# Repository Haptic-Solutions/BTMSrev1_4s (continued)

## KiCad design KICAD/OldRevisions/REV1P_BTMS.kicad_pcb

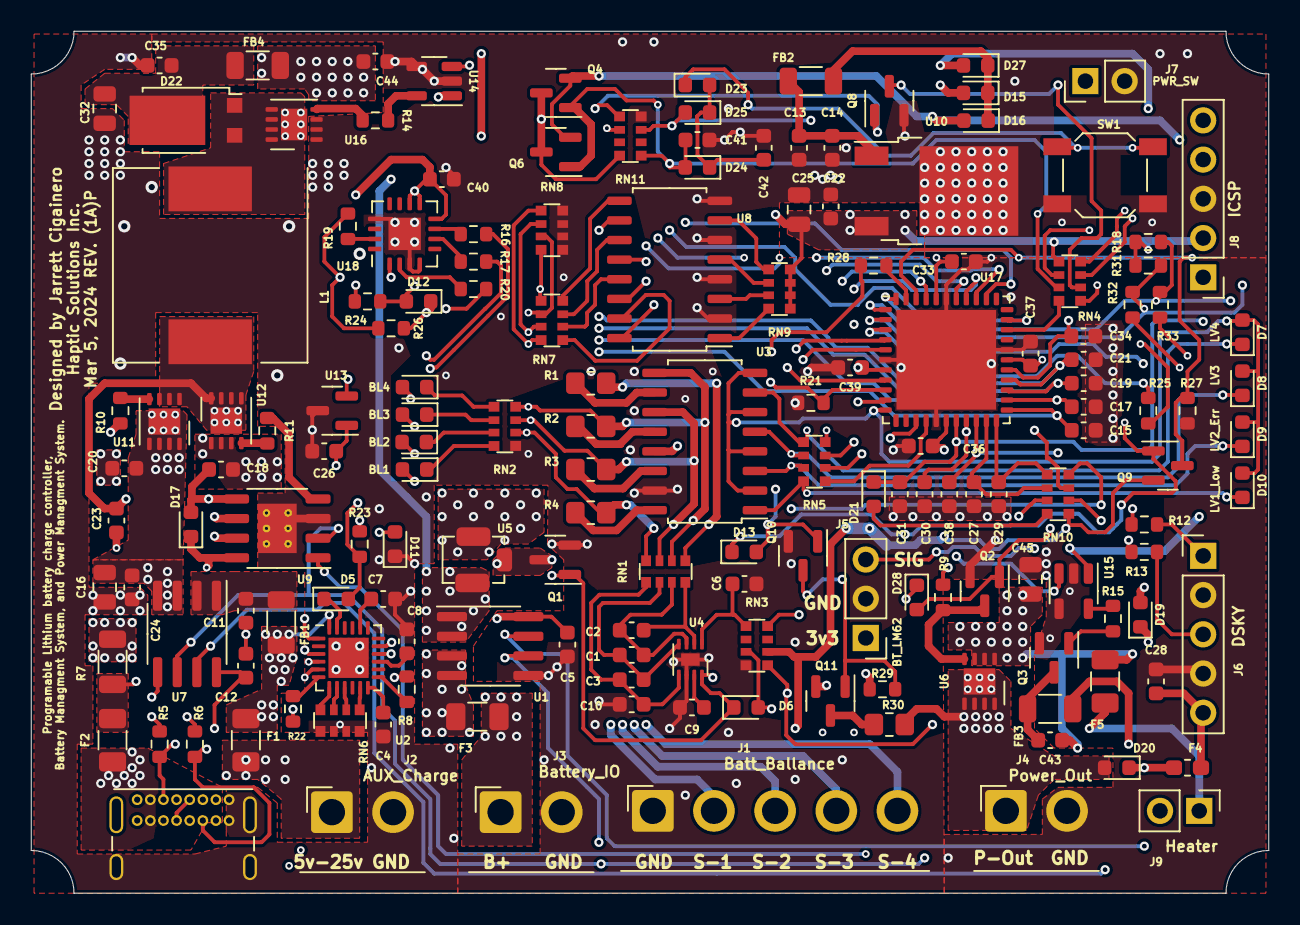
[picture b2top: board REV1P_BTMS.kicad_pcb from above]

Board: 4 copper layers, 80.1 x 55.8 mm, 162 parts (0 on the bottom side), 134 nets.

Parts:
C1, C2, C3, C4, C5, C8, C9, C10, C12, C15, C17, C19, C21, C26, C40, C43: 0.1uf BF; C_0603_1608Metric
C6, C7, C11, C13, C14, C18, C20, C22, C23, C24, C27, C28, C29, C30, C34, C35, C38, C41, C42, C44: 1uf 25v BF; C_0603_1608Metric
C16, C25, C32, C45: 10uf 25v BF; C_0805_2012Metric
C31, C33, C36, C37, C39: 0.1uf film; C_0603_1608Metric
D1: BL4; LED_0603_1608Metric
D2: BL3; LED_0603_1608Metric
D3: BL2; LED_0603_1608Metric
D4: BL1; LED_0603_1608Metric
D5, D6, D13, D15, D16, D17, D19, D20, D21, D23, D24, D25, D27, D28: D_Schottky40V; D_0603_1608Metric
D7: LV4; LED_0603_1608Metric
D8: LV3; LED_0603_1608Metric
D9: LV2_Err; LED_0603_1608Metric
D10: LV1_Low; LED_0603_1608Metric
D11: VB_Stat; LED_0603_1608Metric
D12: Diode40V; D_0603_1608Metric
D22: D_Schottky_AAK; TO-277B
F1, F2, F5: 5A; Fuse_1206_3216Metric
F3: 10A; Fuse_1206_3216Metric
F4: 0A5; Fuse_0603_1608Metric_Pad1.05x0.95mm_HandSolder
FB1, FB2, FB3, FB4: FerriteBead; R_1206_3216Metric
J1: Batt_Ballance; JST_VH_B5PS-VH_1x05_P3.96mm_Horizontal
J2: AUX_Charge; JST_VH_B2PS-VH_1x02_P3.96mm_Horizontal
J3: Battery_IO; JST_VH_B2PS-VH_1x02_P3.96mm_Horizontal
J4: Power_Out; JST_VH_B2PS-VH_1x02_P3.96mm_Horizontal
J5: BT_LM62; PinHeader_1x03_P2.54mm_Vertical
J6: DSKY; PinHeader_1x05_P2.54mm_Vertical
J7: PWR_SW; PinHeader_1x02_P2.54mm_Vertical
J8: ICSP; PinHeader_1x05_P2.54mm_Vertical
J9: Heater; PinHeader_1x02_P2.54mm_Vertical
J10: USB_C_Receptacle_4085; USB_C_Receptacle_GCT_USB4085
L1: 10uH; L_12x12mm_H4.5mm
Q1, Q3: SSM3K341R; SOT-23
Q2, Q8, Q10: DMN65D8L; SOT-23
Q4, Q6, Q9, Q11: FDN340P; SOT-23
R1, R2, R3, R4, R30: 150; R_0805_2012Metric_Pad1.20x1.40mm_HandSolder
R5, R6, R18, R31: 5K1; R_0603_1608Metric
R7: 10mR; R_1206_3216Metric
R8: 10K_NTC; R_0603_1608Metric
R9, R22, R23, R24, R25, R26, R27, R28, R29: 10K; R_0603_1608Metric
R10, R11, R14, R32, R33: 12; R_0603_1608Metric
R12, R13, R15, R16, R17, R19, R20: 27R; R_0603_1608Metric
R21: 91K; R_0603_1608Metric
RN1, RN2, RN3, RN4, RN5, RN6, RN8, RN9, RN10: 1K; R_Array_Convex_4x0612
RN7, RN11: 10K; R_Array_Convex_4x0612
SW1: PTS526; SW_SPST_SKQG_WithStem
U1, U7: ACS711xLCTR-25AB; SOIC-8_3.9x4.9mm_P1.27mm
U2: AP33772; WQFN-24-1EP_4x4mm_P0.5mm_EP2.6x2.6mm
U3, U8: IS281-4; SOIC-16_4.55x10.3mm_P1.27mm
U4: Q294700DSGR; WDFN-8-1EP_2x2mm_P0.5mm_EP0.8x1.2mm
U5: SCF4030-12-0X
U6: AONR21321; DFN-8-1EP_3x3mm_P0.65mm_EP1.7x2.05mm
U9: IRS2184; SOIC-8-1EP_3.9x4.9mm_P1.27mm_EP2.514x3.2mm_ThermalVias
U10: BA033CC0FP-E2; TO-252-2
U11, U12, U16: AON7522E; DFN-8-1EP_3x3mm_P0.65mm_EP1.7x2.05mm
U13: LM62CIM3/NOPB; SOT-23
U14, U15: FAN3100TSX; SOT-23-5
U17: dsPIC30F3011-PT; QFN-44-1EP_8x8mm_P0.65mm_EP6.45x6.45mm
U18: FT230XQ; QFN-16-1EP_4x4mm_P0.65mm_EP2.1x2.1mm

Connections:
+5C: C5.1, C12.1, C22.1, C25.1, C26.1, C33.1, C36.1, C37.1, C39.1, C40.2, D12.1 (K), J5.1, J8.2, Q9.2 (S), R18.1, R23.1, R25.2, R26.2, R31.1, RN3.6 (R3.2), RN4.5 (R4.2), RN9.1 (R1.1), RN9.2 (R2.1), RN9.3 (R3.1), RN9.4 (R4.1), RN10.1 (R1.1), RN11.6 (R3.2), U1.8 (VCC), U7.8 (VCC), U10.3 (VO), U13.1 (G), U17.7 (VDD0), U17.17 (AVDD), U17.28 (VDD1), U17.40 (VDD2), U18.1 (VCCIO), U18.8 (3V3OUT), U18.9 (~RESET), U18.10 (VCC)
/BCsense: C38.1, RN4.6 (R3.2), U17.20 (EMUC3/AN1/VREF-/CN3/RB1)
/BTStrapSig: C23.2, L1.1, U9.6 (VS), U11.1 (S), U11.2 (S), U11.3 (S), U12.5 (D), U12.6 (D), U12.7 (D), U12.8 (D), U12.9 (D)
/BV_Fault: D6.2 (A), RN3.3 (R3.1), U17.36 (~FLTA/INT0/RE8)
/BattIn: F3.2, RN3.8 (R1.2), U1.3 (IP-), U1.4 (IP-)
/Btemp: C27.1, RN10.6 (R3.2), U17.21 (AN2/~SS1/CN4/RB2)
/Btemp_in: J5.3, RN10.3 (R3.1)
/CC1: J10.A5 (CC1), R5.2, U2.17 (CC1)
/CC2: J10.B5 (CC2), R6.2, U2.16 (CC2)
/CCsense: C34.1, RN10.7 (R2.2), U17.27 (AN8/RB8)
/CCsense_in: RN10.2 (R2.1), U7.7 (VIOUT)
/CH_Boost+: U14.3 (IN+), U17.8 (PWM3H/RE5)
/CHctrl+: U9.1 (IN), U17.10 (PWM2H/RE3)
/C_Fault: D13.1 (K), D28.1 (K), Q9.1 (G), RN4.4 (R4.1), U1.6 (~FAULT), U7.6 (~FAULT), U9.2 (~SD)
/C_Fault_In: Q9.3 (D), R27.2, U17.42 (EMUC2/OC1/IC1/INT1/RD0)
/ChargeVoltage: C30.1, D12.2 (A), R24.1, RN3.5 (R4.2), U17.19 (EMUD3/AN0/VREF+/CN2/RB0)
/ExtBus: C43.1, C44.1, C45.1, F5.1, FB4.2, Q11.2 (S), R9.1, R29.1, U5.3 (T2), U6.1 (S), U6.2 (S), U6.3 (S)
/Heat_CTRL: U15.3 (IN+), U17.14 (PWM1H/RE1)
/HighCHfet: R10.2, U11.4 (G)
/IntBus: Q4.3 (D), Q6.3 (D), RN11.8 (R1.2), U1.1 (IP+), U1.2 (IP+), U5.1 (T1)
/IntSwitched: C18.1, D16.2 (A), D17.2 (A), Q4.2 (S), Q6.2 (S), U9.5 (VCC), U14.1 (VDD), U15.1 (VDD)
/KeepAlive: Q8.1 (G), RN11.5 (R4.2), U17.5 (RF0)
/LBatt_Cell_1: D4.2 (A), J1.2, R4.1, RN1.8 (R1.2), RN2.2 (R2.1), U3.13 (out2_E), U8.16 (out1_C)
/LBatt_Cell_2: D3.2 (A), J1.3, R3.1, RN1.7 (R2.2), RN2.3 (R3.1), U3.11 (out3_E), U8.14 (out2_C)
/LBatt_Cell_3: D2.2 (A), J1.4, R2.1, RN1.6 (R3.2), RN2.4 (R4.1), U3.9 (out4_E), U8.12 (out3_C)
/LBatt_Cell_4: D1.2 (A), J1.5, R1.1, RN1.5 (R4.2), U8.10 (out4_C)
/LithCell_V1: C15.1, RN7.8 (R1.2), RN8.1 (R1.1), U17.23 (AN4/QEA/IC7/CN6/RB4)
/LithCell_V2: C17.1, RN7.7 (R2.2), RN8.2 (R2.1), U17.24 (AN5/QEB/IC8/CN7/RB5)
/LithCell_V3: C19.1, RN7.6 (R3.2), RN8.3 (R3.1), U17.25 (AN6/OCFA/RB6)
/LithCell_V4: C21.1, RN7.5 (R4.2), RN8.4 (R4.1), U17.26 (AN7/RB7)
/LowCHfet: R11.2, U12.4 (G)
/MCLR: C31.1, D21.1 (K), J8.1, U17.18 (~MCLR)
/Mult_B1: RN5.1 (R1.1), U17.15 (PWM1L/RE0)
/Mult_B2: RN5.2 (R2.1), U17.37 (EMUD2/OC2/IC2/INT2/RD1)
/Mult_B3: RN5.3 (R3.1), U17.41 (OC3/RD2)
/Mult_B4: RN5.4 (R4.1), U17.38 (OC4/RD3)
/Mult_SEL: D7.2 (A), D8.2 (A), D9.2 (A), D10.2 (A), U3.2 (in1_C), U3.4 (in2_C), U3.6 (in3_C), U3.8 (in4_C), U17.11 (PWM2L/RE2)
/PGMC: J8.5, R31.2, R32.1, U17.1 (PGC/EMUC/U1RX/SDI1/SDA/RF2)
/PGMD: J8.4, R18.2, R33.1, U17.44 (PGD/EMUD/U1TX/SDO1/SCL/RF3)
/PO_EN: D28.2 (A), Q2.1 (G), RN4.1 (R1.1)
/Pctrl_IN: Q8.3 (D), RN4.2 (R2.1)
/Pctrl_OUT: C41.1, D24.2 (A), Q4.1 (G), Q6.1 (G), RN4.7 (R2.2), RN11.1 (R1.1)
/PowerOutEnable: RN4.8 (R1.2), U17.31 (OSC2/CLKO/RC15)
/PowerOutput: D20.2 (A), D27.2 (A), J4.1, R30.2, U6.5 (D), U6.6 (D), U6.7 (D), U6.8 (D), U6.9 (D)
/Pre_Charge: R28.1, U17.43 (SCK1/RF6)
/U1RX: R19.2, R26.1, U17.35 (EMUC1/SOSCO/T1CK/U1ARX/CN0/RC14)
/U1TX: R20.2, U17.32 (EMUD1/SOSCI/T2CK/U1ATX/CN1/RC13)
/U2RX: R12.2, R25.1, U17.3 (U2RX/CN17/RF4)
/U2TX: R13.2, U17.2 (U2TX/CN18/RF5)
/USB_D+: J10.A6 (D+), J10.B6 (D+), R17.1
/USB_D-: J10.A7 (D-), J10.B7 (D-), R16.1
/V_Bus_Stat: D5.2 (A), R21.2, R23.2, U17.9 (PWM3L/RE4)
/__PwrKey: D25.2 (A), RN11.3 (R3.1), U17.4 (RF1)
GND: C4.2, C5.2, C6.2, C7.2, C8.2, C9.2, C10.2, C11.2, C12.2, C13.2, C14.2, C15.2, C16.2, C17.2, C18.2, C19.2, C20.2, C21.2, C22.2, C24.2, C25.2, C26.2, C27.2, C28.2, C29.2, C30.2, C31.2, C32.2, C33.2, C34.2, C35.2, C36.2, C37.2, C38.2, C39.2, C40.1, C41.2, C42.2, C44.2, C45.2, D11.1 (K), J1.1, J2.2, J3.2, J4.2, J5.2, J6.2, J6.4, J7.2, J8.3, J10.A1 (GND), J10.A12 (GND), J10.B1 (GND), J10.B12 (GND), J10.S1 (SHIELD), Q1.2 (S), Q2.2 (S), Q3.2 (S), Q8.2 (S), Q10.2 (S), R5.1, R6.1, R8.1, R21.1, R27.1, RN2.1 (R1.1), RN3.4 (R4.1), RN6.5 (R4.2), RN6.6 (R3.2), RN6.7 (R2.2), RN6.8 (R1.2), RN8.5 (R4.2), RN8.6 (R3.2), RN8.7 (R2.2), RN8.8 (R1.2), RN11.4 (R4.1), SW1.1 (A), U1.5 (GND), U2.3 (GND), U2.25 (PAD), U3.15 (out1_E), U4.6 (VSS), U4.9 (PAD), U7.5 (GND), U8.2 (in1_C), U8.4 (in2_C), U8.6 (in3_C), U8.8 (in4_C), U9.3 (COM), U9.9 (PAD), U10.2 (GND), U12.1 (S), U12.2 (S), U12.3 (S), U13.3 (S), U14.2 (GND), U14.4 (XREF), U15.2 (GND), U15.4 (XREF), U16.1 (S), U16.2 (S), U16.3 (S), U17.6 (VSS0), U17.16 (AVSS), U17.29 (VSS1), U17.39 (VSS2), U17.45 (PAD), U18.3 (GND), U18.4 (~CTS), U18.13 (GND), U18.17 (GND)
unnamed: C1.1, C3.2, RN1.2 (R2.1), U4.4 (V2)
unnamed: C1.2, C2.1, RN1.3 (R3.1), U4.3 (V3)
unnamed: C2.2, RN1.4 (R4.1), U4.2 (V4)
unnamed: C6.1, RN3.1 (R1.1), U4.1 (VDD)
unnamed: C7.1, U2.20 (V5V)
unnamed: C8.1, U2.15 (IFB)
unnamed: C9.1, U4.7 (CD)
unnamed: C3.1, C10.1, RN1.1 (R1.1), U4.5 (V1)
unnamed: C11.1, FB1.2, U7.1 (IP+), U7.2 (IP+)
unnamed: C13.1, C14.1, FB2.2, U10.1 (VI)
unnamed: C16.1, C20.1, C24.1, U7.3 (IP-), U7.4 (IP-), U11.5 (D), U11.6 (D), U11.7 (D), U11.8 (D), U11.9 (D)
unnamed: C23.1, D17.1 (K), U9.8 (VB)
unnamed: C28.1, F4.2, J6.5
unnamed: C29.1, RN10.5 (R4.2), U17.22 (AN3/INDX/CN5/RB3)
unnamed: C32.1, C35.1, D22.3 (K), FB4.1
unnamed: C42.1, D23.2 (A), D24.1 (K), D25.1 (K)
unnamed: C43.2, FB3.1, Q3.3 (D)
unnamed: D1.1 (K), RN2.5 (R4.2)
unnamed: D2.1 (K), RN2.6 (R3.2)
unnamed: D3.1 (K), RN2.7 (R2.2)
unnamed: D4.1 (K), RN2.8 (R1.2)
unnamed: D5.1 (K), U2.23 (PWR_EN)
unnamed: D6.1 (K), Q1.1 (G), U4.8 (OUT)
unnamed: D7.1 (K), RN5.5 (R4.2), U3.7 (in4_A)
unnamed: D8.1 (K), RN5.6 (R3.2), U3.5 (in3_A)
unnamed: D9.1 (K), RN5.7 (R2.2), U3.3 (in2_A)
unnamed: D10.1 (K), RN5.8 (R1.2), U3.1 (in1_A)
unnamed: D11.2 (A), R22.1
unnamed: D13.2 (A), Q10.1 (G), R28.2
unnamed: D15.1 (K), D16.1 (K), D27.1 (K), FB2.1
unnamed: D19.1 (K), D20.1 (K), F4.1
unnamed: D21.2 (A), RN10.8 (R1.2)
unnamed: D22.1 (A), D22.2 (A), L1.2, U16.5 (D), U16.6 (D), U16.7 (D), U16.8 (D), U16.9 (D)
unnamed: D23.1 (K), J7.1, SW1.2 (B)
unnamed: F1.1, J2.1
unnamed: F2.1, J10.A4 (VBUS), J10.A9 (VBUS), J10.B4 (VBUS), J10.B9 (VBUS)
unnamed: F2.2, R7.2, U2.1 (ISENP)
unnamed: F3.1, J3.1
unnamed: F5.2, J9.1
unnamed: FB3.2, J9.2
unnamed: J6.1, R12.1
unnamed: J6.3, R13.1
unnamed: Q1.3 (D), U5.2 (Trig)
unnamed: Q2.3 (D), R9.2, U6.4 (G)
unnamed: Q3.1 (G), R15.2
unnamed: Q10.3 (D), Q11.1 (G), R29.2
unnamed: Q11.3 (D), R30.1
unnamed: R1.2, U3.10 (out4_C)
unnamed: R2.2, U3.12 (out3_C)
unnamed: R3.2, U3.14 (out2_C)
unnamed: R4.2, U3.16 (out1_C)
unnamed: R8.2, U2.13 (OTP)
unnamed: R10.1, U9.7 (HO)
unnamed: R11.1, U9.4 (LO)
unnamed: R14.1, U16.4 (G)
unnamed: R14.2, U14.5 (OUT)
unnamed: R15.1, U15.5 (OUT)
unnamed: R16.2, U18.7 (USBDM)
unnamed: R17.2, U18.6 (USBDP)
unnamed: R19.1, U18.15 (TXD)
unnamed: R20.1, U18.2 (RXD)
unnamed: R22.2, U2.6 (GPIO4)
unnamed: RN4.3 (R3.1), U1.7 (VIOUT)
unnamed: RN7.1 (R1.1), U8.15 (out1_E)
unnamed: RN7.2 (R2.1), U8.13 (out2_E)
unnamed: RN7.3 (R3.1), U8.11 (out3_E)
unnamed: RN7.4 (R4.1), U8.9 (out4_E)
unnamed: RN9.5 (R4.2), U8.7 (in4_A)
unnamed: RN9.6 (R3.2), U8.5 (in3_A)
unnamed: RN9.7 (R2.2), U8.3 (in2_A)
unnamed: RN9.8 (R1.2), U8.1 (in1_A)
unnamed: RN10.4 (R4.1), U13.2 (D)
unnamed: R32.2, U2.4 (SDA)
unnamed: R33.2, U2.5 (SCL)
unnamed: RN6.4 (R4.1), U2.7 (GPIO2)
unnamed: RN6.3 (R3.1), U2.8 (GPIO1)
unnamed: RN6.2 (R2.1), U2.9 (GPIO3)
unnamed: RN6.1 (R1.1), U2.11 (GPIO5)
unnamed: C4.1, U2.12 (V3VD)
VBUS: D15.2 (A), D19.2 (A), F1.2, FB1.1, R7.1, R24.2, U2.24 (VCC)

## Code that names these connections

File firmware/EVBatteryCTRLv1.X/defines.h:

/*Copyright (c) <2024> <Jarrett Cigainero>

Permission is hereby granted, free of charge, to any person obtaining a copy
of this software and associated documentation files (the "Software"), to deal
in the Software without restriction, including without limitation the rights
to use, copy, modify, merge, publish, distribute, sublicense, and/or sell
copies of the Software, and to permit persons to whom the Software is
furnished to do so, subject to the following conditions:

The above copyright notice and this permission notice shall be included in all
copies or substantial portions of the Software.

THE SOFTWARE IS PROVIDED "AS IS", WITHO70054eUT WARRANTY OF ANY KIND, EXPRESS OR
IMPLIED, INCLUDING BUT NOT LIMITED TO THE WARRANTIES OF MERCHANTABILITY,
FITNESS FOR A PARTICULAR PURPOSE AND NONINFRINGEMENT. IN NO EVENT SHALL THE
AUTHORS OR COPYRIGHT HOLDERS BE LIABLE FOR ANY CLAIM, DAMAGES OR OTHER
LIABILITY, WHETHER IN AN ACTION OF CONTRACT, TORT OR OTHERWISE, ARISING FROM,
OUT OF OR IN CONNECTION WITH THE SOFTWARE OR THE USE OR OTHER DEALINGS IN THE
SOFTWARE. */

#ifndef DEFINES_H
#define	DEFINES_H
//##############################################################################
// Tm = 32767 * (1 / (((clkSpeedmhz * PLL) / 4) / tiksPerIRQ))
//#define IPS 29.48;   //million instructions per second.
#define IPS 14.74   //million instructions per second.
//Analog
#define sample_Average 2
//PWM period
#define PWM_Period 100
#define PWM_MaxHeat (PWM_Period*2)*0.9
#define PWM_MaxChrg (PWM_Period*2)*0.98
#define PWM_MaxBoost_LO 0.52
#define PWM_MaxBoost_HI 0.72
#define PWM_MaxBoost_LN (PWM_Period*2)*PWM_MaxBoost_LO
#define PWM_MaxBoost_HN (PWM_Period*2)*PWM_MaxBoost_HI
//Charger
#define charge_Max_Level 0.65
#define C_Min_Voltage 3.0
//#define IPS 7.37   //million instructions per second.
#define BAUD1 9600  //Default BAUD rate for PORT 1
#define BAUD2 9600  //Default BAUD rate for PORT 2
#define calc_125 0.00003472 //Value for calculating the total current in and out of battery every second.
//Firmware Version String
#define version "\n\rFirmware: V0.1-Dev\n\r2S-4S Compatible Cell Configs.\n\r(C) Haptic Solutions Inc. (2024)\n\r"
//IO inputs
#define PWR_SW !PORTFbits.RF1 //Power on/off switch, button, or key. Active low input.
#define BV_Fault PORTEbits.RE8  //Battery Voltage Fault.
#define C_Fault PORTDbits.RD0 //Battery or charge input/output current fault.
//Analog inputs
#define ChargeVoltage ADCBUF0 //Voltage
#define BCsense ADCBUF1 //Current
#define Btemp ADCBUF2 //Batt Temp
#define Mtemp ADCBUF3 //My Temp
#define LithCell_V1 ADCBUF4 //Cell 1 Volts
#define LithCell_V2 ADCBUF5 //Cell 2 Volts
#define LithCell_V3 ADCBUF6 //Cell 3 Volts
#define LithCell_V4 ADCBUF7 //Cell 4 Volts
#define CCsense ADCBUF8 //CCsense
//IO outputs
#define KeepAlive LATFbits.LATF0 //Enables power to self and system.
#define Cell_Volt LATEbits.LATE4 //Cell voltage sense enable.
#define PowerOutPreCharge LATFbits.LATF6 //Power output pre-charge control
#define PowerOutEnable LATCbits.LATC15 //Power output enable.
//LED outputs
#define Mult_SEL LATEbits.LATE2 //LED and Cell ballance multiplexed select.
#define Mult_B1 LATEbits.LATE0
#define Mult_B3 LATDbits.LATD2
#define Mult_B2 LATDbits.LATD1
#define Mult_B4 LATDbits.LATD3
#define LED_dir_1 TRISE
#define LED_dir_2 TRISD
#define LED_HiZ_1 PWM_TRIS_DIR | 0x0001
#define LED_HiZ_2 GENERAL3_DIR | 0x000E
#define DFLT_1 PWM_TRIS_DIR
#define DFLT_2 GENERAL3_DIR

#define Heat_CTRL PDC1  //Heater PWM.
#define CHctrl PDC2     //Charge buck PWM.
#define CH_Boost PDC3   //Charge boost PWM.

//IO
#define ANALOG_DIR 0x01FF
#define ANALOG_TRIS TRISB
#define ANALOG_LAT LATB
#define ANALOG_PORT PORTB

#define GENERAL1_DIR 0x1FFF
#define GENERAL1_TRIS TRISC
#define GENERAL1_LAT LATC
#define GENERAL1_PORT PORTC

#define GENERAL2_DIR 0xFFBE
#define GENERAL2_TRIS TRISF
#define GENERAL2_LAT LATF
#define GENERAL2_PORT PORTF

#define GENERAL3_DIR 0xFFF1
#define GENERAL3_TRIS TRISD
#define GENERAL3_LAT LATD
#define GENERAL3_PORT PORTD

#define PWM_TRIS_DIR 0xFFEA
#define PWM_TRIS TRISE
#define PWM_LAT LATE
#define PWM_PORT PORTE

//Memory Defines
/* This assumes the compiler puts the stack at the end of memory space just after
 * the user variables and the stack pointer counts up */
#define ramSize 0x07F0 //Size of memory.
#define ramAddressStart 0x0800  //Where the dsPIC30F4011's ram address starts.
#define stackFaultMax ramSize + ramAddressStart - 1
#define ramFree (ramSize + ramAddressStart) - 2 //Minus 15 bytes of ram. If the stack intrudes on this then it should throw an error code before a complete system crash and undefined behavior.

//General
#define yes 1
#define no 0
#define none 0
#define Ltest 4
#define Debug 3
#define Ballance 2
#define on 1
#define off 0
#define set 1
#define clear 0
#define NULL 0
#define input 1
#define output 0
#define maxFCodes 20
#define I_Auto -1

//Constants
#define Max_Cell_Count 4
#define SOC_Cycles 8
#define AuxFuse 5       //Aux charge port fuse rating placeholder.
#define PreChargeTime 2 //Output pre-charge timer placeholder.
#define LED_Brightness 10
#define V_REF 3.35      //Measured reference voltage placeholder

//Run Levels
#define Shutdown 0
#define Crit_Err 1
#define Heartbeat 2
#define Cal_Mode 3
#define On_W_Err 4
#define All_Sys_Go 5

//Charge Session Levels
#define UnknownStart 0
#define EmptyStart 1
#define FullStart 2

//Heater calibration states.
#define notrun 0
#define initialize 1
#define calibrating 2
#define ready 3
#define error 4
#define disabled 5

//Charger modes.
#define CHError 0
#define Stop 1
#define Wait 2
#define Assignment_Ready 3
#define USB2 4
#define USB3_Wimp 5
#define USB3 6
#define USB3_Fast 7
#define Solar 8
//Charger limits
#define cycleLimit 4

//OSC modes
#define slow 0
#define fast 1

//Power switch modes
#define push_and_hold 0         //Push button switch
#define toggle_switch 1         //Toggle switch
#define on_with_charger 2       //??? what would you use this for?
#define off_with_charger 3      //Solar light, or Emergency light mode.

#define gauge_timer 100

//##############################################################################
#endif

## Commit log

2024-02-10 Re-added new files.
2024-02-12 Updated PDF schematic
2024-02-12 Updated PDF schematic.
2024-02-12 Removed files.
2024-02-12 Changed secondary protection to use triggable fuse. Restructured repo.
2024-02-12 Updated schematic and readme files.
2024-02-13 Updated schematic.
2024-02-13 Cleaned up some things in schematic. Switched to a larger grid size. Using different USB-C power trigger chip.
2024-02-14 Added connectors to schematic. Updated firmware to accomodate new featers, and omit unneeded features.
2024-02-14 Updated some capacitors for correct voltage values.
2024-02-14 Started working on PCB layout.
2024-02-14 Fixed 3.3v regulator not having correct pinout. Progressed board layout.
2024-02-15 Shrunk silkscreen text to compact parts more.
2024-02-16 Started running traces.
2024-02-16 Continued routing.
2024-02-16 Continued routing board.
2024-02-17 Board routing complete and cleaned up all board DRV violations except some silkscreen warning on the bottom edge.
2024-02-17 Added backside ground planes.
2024-02-17 Cleaned up ground plane islands.
2024-02-17 Extended board and placed mounting points.
2024-02-17 Cleaned up connector silkscreens. No more DRC warnings.
2024-02-17 Added groundplanes to front and middle layer. Cleaned up islands and tails.
2024-02-17 Added solder mask and solder paste lines for high-current traces.
2024-02-18 Cleaned up some things.
2024-02-18 Extended front groundplane and cleaned up islands and tails.
2024-02-18 Added power switch button. Added credits and description silkscreening.
2024-02-18 Added g-code files for board.
2024-02-19 Added parts list order.
2024-02-19 Fixed mirrored silkscreen on back layer.
2024-02-19 Cleaned up more tails and islands.
2024-02-19 Cleaned up more tails and islands on PCB.
2024-02-19 Added 10K pullup resistors to dsPIC's serial RX lines.
2024-02-19 Added ground connection to CTS pin on FTDI chip.
2024-02-19 Cleaned up some things. Price optimized capacitors.
2024-02-19 Widened a trace for charge input.
2024-02-19 Removed unneeded 15V zener diodes. Added pre-charge circuit to output to reduce inrush current. Removed power control circuit from FTDI chip. Fixed USB-C connector.
2024-02-19 Cleaned up some things. Added silkscreen artwork to back.
2024-02-25 Continued porting firmware to new hardware.
2024-02-25 Refactored auto shutdown and some timer processes.
2024-02-25 Refactoring and optimizing some things. Need to get overall memory usage down.
2024-02-26 Added LED and Ballance features.
2024-02-27 Refactored some things.
2024-02-27 Added charge cycle counter, and battery capacity reduction based on cycles accumulated.
2024-02-28 Fixed bugs caused by enabling compiler optimizations such as the address error fault when trying to access NVM or PGM memories.
2024-03-04 Fixed chip resistor array footprints. <- Need to finish re-routing traces and update G-Code files.
2024-03-05 Finished routing for fixed resistor array footprints. Added I2C lines to USB-3 PD chip to dsPIC. Cleaned up ground-plane islands and tails.
2024-03-06 Updated revision and date code.
2024-03-09 Got firmware somewhat functional and kinda stable. Still crashes sometimes but fails gracefully enough to not damage anything. Need to finish updating schematic and board layout.
2024-03-10 Fixed a few bugs with initialization of first run variables. Added charging system recycle error code and stop/reset function.
2024-03-11 Fixed HUD routines.
2024-03-11 Added LED test and fixed cell ballance driver output.
2024-03-11 Refactored exception handling code to be more robust.
2024-03-12 Added to-do and test files.
2024-03-14 Began expirimenting with clock switching to reduce power draw. Managed to double idle runtime. Started runtime calculations. Fixed some things in schematic.
2024-03-21 Rerouted board after making changes to schematic.
2024-03-21 Fixed power button not having a signal to dsPIC.
2024-03-21 Cleaned up ground-plane tails and islands. Added high-current paths using solder mask zones. Updated hardware todo list.
2024-03-21 Added text to LED indicators.
2024-03-21 Added four 10uF capacitors to ExtBus. Rerouted some things.
2024-03-22 Fixed P-Channel mosfets on ballance circuit and cell voltage front-end being connected backwards in schematic.
2024-03-26 Cleaned up some things and shifted some parts and traces around.
2024-03-26 Cleaned up and added more high current paths.
2024-03-27 Cleaned up more groundplane islands and tails.
2024-04-06 Cleaned up some things. Added capacitor after D1 Reviewed design for next revision prototype build.
2024-04-30 Cleaned up some thing and adjust some resistor values in board design. Testing design is going well. Need to power current sense IC's directly or through mosfet. Need to add level shifter inline with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
2024-05-01 Changed firmware to use average cell voltage for HV detect rountine. Was too sensitive to noise before. Added attributes paramter to error code system. Made error codes a little more verbose. Changed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
2024-05-06 Fixed problem where charge mosfet driver chip needs 5V logic levels to work. Replaced driver chip config pull-down resistor with solderable jumper pad. Removed 100 ohm resistor on dsPIC analog voltag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
2024-05-06 Added pre-charge circuit for output. Added automatic Cell count function to firmware.
2024-05-22 Added USB-PD support to firmware via I2C. Testing. Fixed bug where system would keep getting open circuit voltage when it's not supposed to causing battery % to jump around. Changed settings unlock c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
2024-05-22 Updated schematic and board to reflect changes made on prototype.
2024-05-22 Cleaned up some things in schematic and board. Deleted files not needed that were added to repo by mistake. Added 30uF of capacitors to input side of buck-boost converter.
2024-05-23 Updated REV1B(P)_schematic. Made copy of REV1A(P) schematic and board layout. Found a few diodes to be leaking current when in sleep mode. Need to fix.
2024-05-27 Cleaned up some files. Refactored parts of firmware. Improved speed of initial compensation stage. Changed open circuit voltage routine to only run on first startup. Added room for more types of volt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
2024-06-10 Revamped setting and information print page. Added settings editing command. Fixed bug where serial ports would sometimes skip data or text output. Added automatic battery evaluation system. Keep an 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
2024-06-10 Updated firmware todo list.
2024-06-10 Fix bug where analog charger current input was using the same variable for 1s 8 sample averaging routine. Changed variable names to make less confusing. Added auto info readout on auto-evaluation eve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
2024-06-12 Clearing things out.
2024-06-12 Reupload newest version.
2024-06-12 Updated commands and fault code info
2024-06-12 Updated command and faultcode info
2024-06-12 Updated command and faultcode files
2024-06-12 Added charge/discharge slowdown based on board temperature to existing battery charge/discharge temperature slowdown Fixed bug where blinkn' lights would sometimes blink erraticlly when a HUD was ena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
2024-06-13 Added 8s charger ready timer to auto-evaluation.
2024-06-19 remove old files
2024-06-19 Reorganize everything.
2024-06-21 Added I2C ADC to REV.1B board. Added Battery Disconnect system to REV.1B board. Changed some dsPIC IO around to reflect changes. Changed power control system to not drain battery very quickly if swit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
2024-07-10 Updated board layout for REV. B Completed initial routing. Need to finish fixing circuit changes such as inrush current limiting. Need to refine board layout.
2024-07-11 Worked on improving routing.
2024-07-11 Finished implementing inrush current limiting changes. Need to verify design. Need to clean up tails and islands. Need to create BOM.
2024-07-11 Updated Revision date.
2024-07-19 Replaced USB-C input diode with P-Channel MOSFET array controlled by dsPIC and USB-PD chip. Added IO expanded chip for dsPIC and USB-C input control interface. Moved some things around on board layou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
2024-07-22 Cleaned up board some. Updated todo files.
2024-10-16 Updated project to KiCad > 8.0 Testing new design... Generated new BOM. Generated new schematic PDF. Generated new STEP file. Generated new GERBER files.
